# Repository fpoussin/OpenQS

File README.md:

OpenQS
======

OSHW quick-shifter.

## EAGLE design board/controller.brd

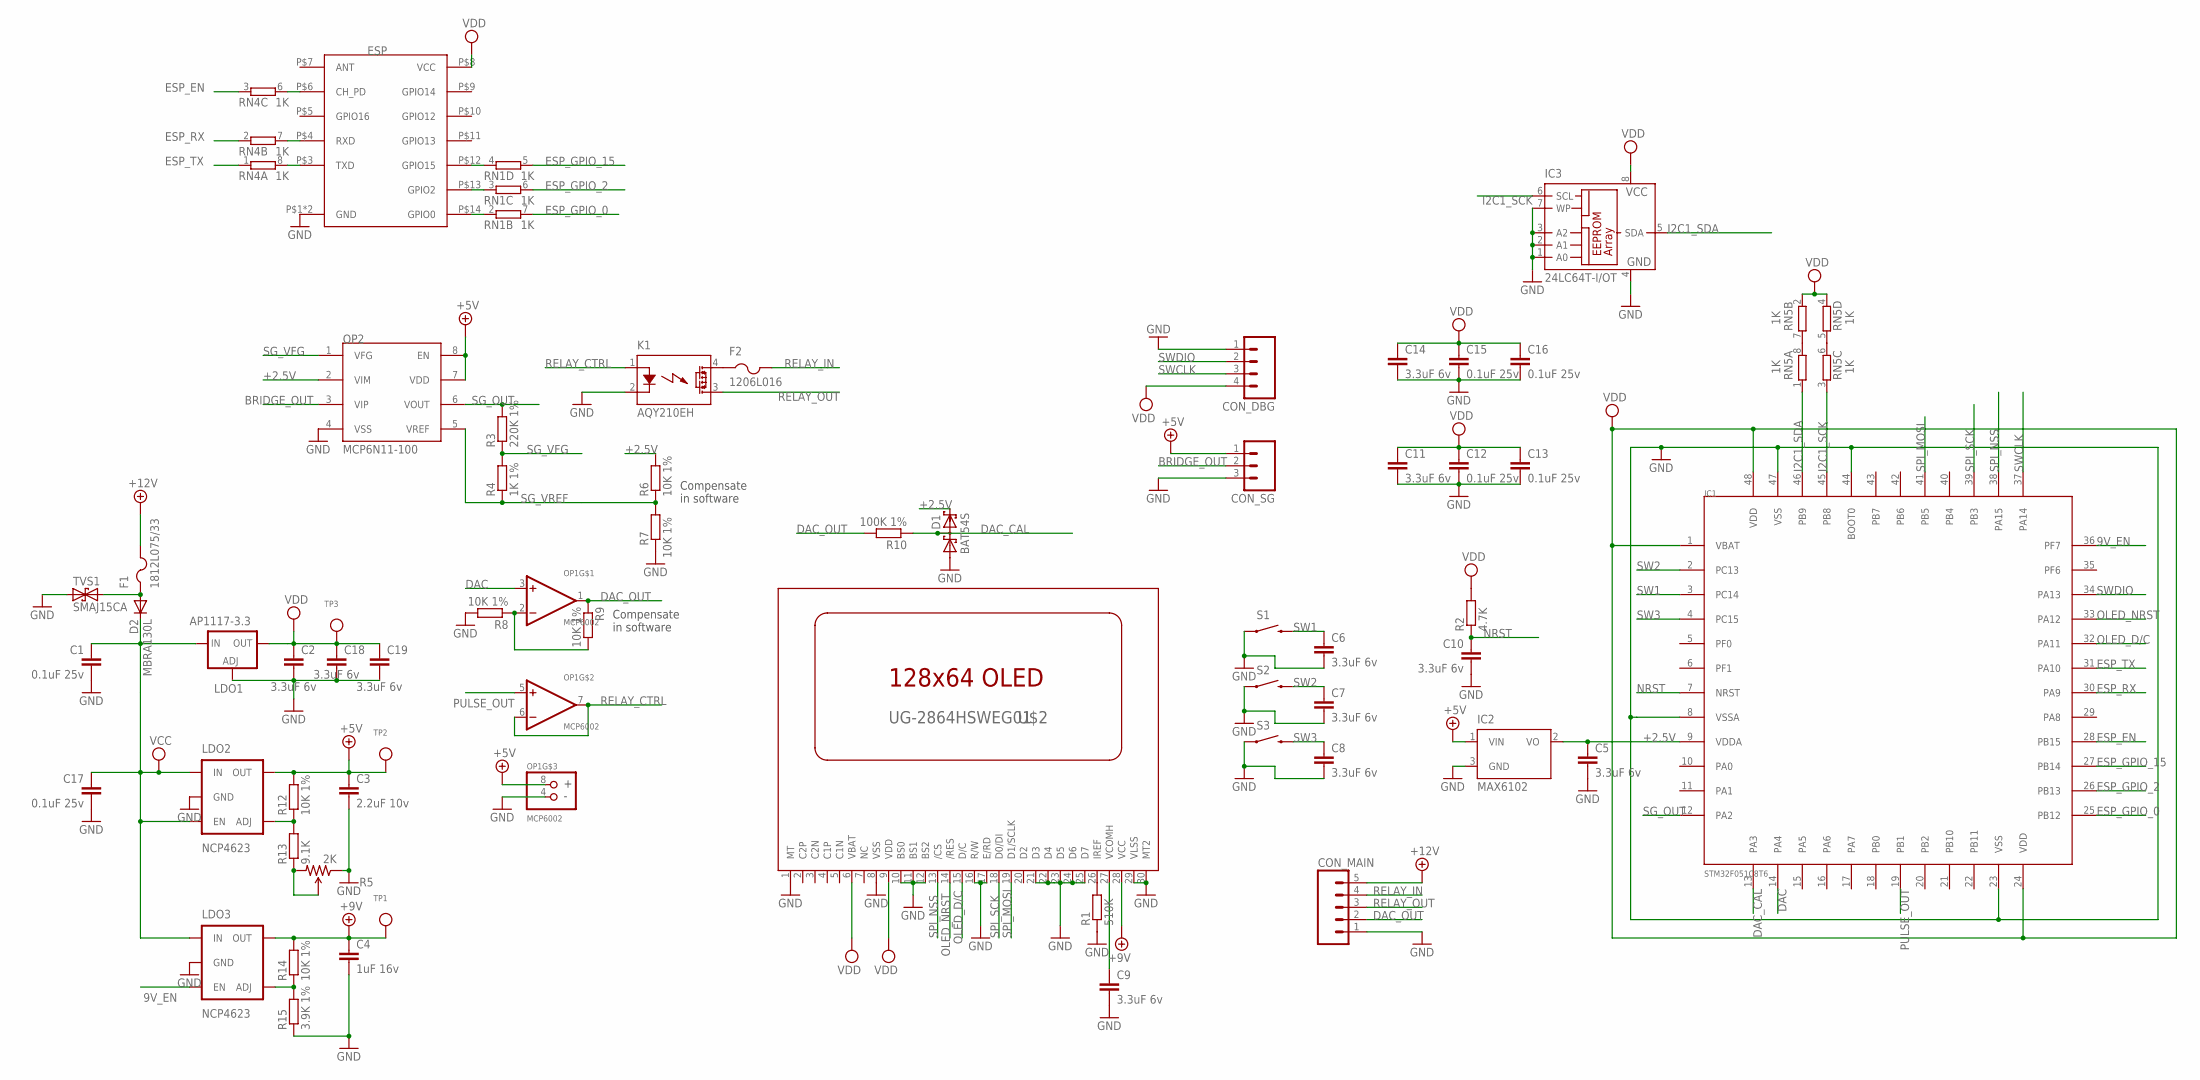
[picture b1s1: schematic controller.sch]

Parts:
C1, C12, C13, C15, C16, C17: 0.1uF 25v; C0603
C2, C5, C6, C7, C8, C9, C10, C11, C14, C18, C19: 3.3uF 6v; C0603
C3: 2.2uF 10v; C0603
C4: 1uF 16v; C0603
CON_DBG: M04LOCK; 1X04_LOCK
CON_MAIN: M05LOCK; 1X05_LOCK
CON_SG: M03LOCK; 1X03_LOCK
D1: BAT54S; SOT23
D2: MBRA130L; SMA-DIODE
ESP: ESP8266; ESP-03
F1: 1812L075/33; 1812
F2: 1206L016; R1206
IC1: STM32F051C8T6; LQFP-48
IC2: MAX6102; SOT23
IC3: 24LC64T-I/OT; SO-08
K1: AQY210EH; SOP04
LDO1: AP1117-3.3; DPACK
LDO2, LDO3: NCP4623; SOT23-5
OP1: MCP6002; MSOP-8
OP2: MCP6N11-100; SO08
R1: 510K; R0603
R2: 4.7K; R0603
R3: 220K 1%; R0603
R4: 1K 1%; R0603
R5: 2K; TRIMPOT-3MM-2
R6, R7, R8, R9, R12, R14: 10K 1%; R0603
R10: 100K 1%; R0603
R13: 9.1K; R0603
R15: 3.9K 1%; R0603
RN1, RN4, RN5: 1K; CAY16
S1, S2, S3: SWITCH-MOMENTARY-2SMD-2; TACTILE_SWITCH_SMD-2
TP1, TP2, TP3: TESTPOINTROUND2MM; TESTPOINT_ROUND_2MM
TVS1: SMAJ15CA; SMA-DIODE
U$2: UG-2864HSWEG01; 1X30-0.7MM

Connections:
9V_EN: IC1.36 (PF7), LDO3.5 (EN)
+2.5V: C5.1, D1.2 (C2), IC1.9 (VDDA), IC2.2 (VO), OP2.2 (VIM), R6.2
+5V: C3.1, CON_SG.1, IC2.1 (VIN), LDO2.1 (OUT), OP1.8 (+), OP2.7 (VDD), OP2.8 (EN), R12.2, TP2.P$1
+9V: C4.1, LDO3.1 (OUT), R14.2, TP1.P$1, U$2.28 (VCC)
+12V: CON_MAIN.5, F1.2
BRIDGE_OUT: CON_SG.2, OP2.3 (VIP)
DAC: IC1.14 (PA4), OP1.3 (+IN)
DAC_CAL: D1.3 (C1A2), IC1.13 (PA3), R10.1
DAC_OUT: CON_MAIN.2, OP1.1 (OUT), R9.1, R10.2
ESP_EN: IC1.28 (PB15), RN4.3 (1)
ESP_GPIO_0: IC1.25 (PB12), RN1.7 (2)
ESP_GPIO_2: IC1.26 (PB13), RN1.6 (2)
ESP_GPIO_15: IC1.27 (PB14), RN1.5 (2)
ESP_RX: IC1.30 (PA9), RN4.2 (1)
ESP_TX: IC1.31 (PA10), RN4.1
GND: C1.2, C2.2, C3.2, C4.2, C5.2, C6.2, C7.2, C8.2, C9.2, C10.2, C11.2, C12.2, C13.2, C14.2, C15.2, C16.2, C17.2, C18.2, C19.2, CON_DBG.1, CON_MAIN.1, CON_SG.3, D1.1 (A1), ESP.P$1 (GND), ESP.P$2 (GND), IC1.8 (VSSA), IC1.23 (VSS), IC1.44 (BOOT0), IC1.47 (VSS), IC2.3 (GND), IC3.1 (A0), IC3.2 (A1), IC3.3 (A2), IC3.4 (GND), IC3.7 (WP), K1.2 (K), LDO1.1 (ADJ), LDO2.2 (GND), LDO3.2 (GND), OP1.4 (-), OP2.4 (VSS), R1.1, R5.1 (CCW), R7.1, R8.2, R15.1, S1.2 (1), S2.2 (1), S3.2 (1), TVS1.A (1), U$2.1 (MT), U$2.8 (VSS), U$2.10 (BS0), U$2.11 (BS1), U$2.12 (BS2), U$2.16 (R/W), U$2.17 (E/RD), U$2.21 (D3), U$2.22 (D4), U$2.23 (D5), U$2.24 (D6), U$2.25 (D7), U$2.29 (VLSS), U$2.30 (MT2)
I2C1_SCK: IC1.45 (PB8), IC3.6 (SCL), RN5.3 (1)
I2C1_SDA: IC1.46 (PB9), IC3.5 (SDA), RN5.1
unnamed: OP1.2 (-IN), R8.1, R9.2
unnamed: C9.1, U$2.27 (VCOMH)
unnamed: R1.2, U$2.26 (IREF)
unnamed: D2.A, F1.1, TVS1.C (2)
unnamed: F2.1, K1.4 (DS1)
unnamed: LDO2.4 (ADJ), R12.1, R13.2
unnamed: LDO3.4 (ADJ), R14.1, R15.2
unnamed: R5.2 (WIPER), R5.3 (CW), R13.1
unnamed: ESP.P$14 (GPIO0), RN1.2 (1)
unnamed: ESP.P$13 (GPIO2), RN1.3 (1)
unnamed: ESP.P$12 (GPIO15), RN1.4 (1)
unnamed: ESP.P$3 (TXD), RN4.8 (2)
unnamed: ESP.P$6 (CH_PD), RN4.6 (2)
unnamed: ESP.P$4 (RXD), RN4.7 (2)
unnamed: RN5.7 (2), RN5.8 (2)
unnamed: RN5.5 (2), RN5.6 (2)
NRST: C10.1, IC1.7 (NRST), R2.1
OLED_D/C: IC1.32 (PA11), U$2.15 (D/C)
OLED_NRST: IC1.33 (PA12), U$2.14 (/RES)
PULSE_OUT: IC1.19 (PB1), OP1.5 (+IN)
RELAY_CTRL: K1.1 (A), OP1.6 (-IN), OP1.7 (OUT)
RELAY_IN: CON_MAIN.4, F2.2
RELAY_OUT: CON_MAIN.3, K1.3 (DS2)
SG_OUT: IC1.12 (PA2), OP2.6 (VOUT), R3.2
SG_VFG: OP2.1 (VFG), R3.1, R4.2
SG_VREF: OP2.5 (VREF), R4.1, R6.1, R7.2
SPI_MOSI: IC1.41 (PB5), U$2.19 (D1/SCLK)
SPI_NSS: IC1.38 (PA15), U$2.13 (/CS)
SPI_SCK: IC1.39 (PB3), U$2.18 (D0/DI)
SW1: C6.1, IC1.3 (PC14), S1.1 (2)
SW2: C7.1, IC1.2 (PC13), S2.1 (2)
SW3: C8.1, IC1.4 (PC15), S3.1 (2)
SWCLK: CON_DBG.3, IC1.37 (PA14)
SWDIO: CON_DBG.2, IC1.34 (PA13)
VCC: C1.1, C17.1, D2.C, LDO1.3 (IN), LDO2.3 (IN), LDO2.5 (EN), LDO3.3 (IN)
VDD: C2.1, C11.1, C12.1, C13.1, C14.1, C15.1, C16.1, C18.1, C19.1, CON_DBG.4, ESP.P$8 (VCC), IC1.1 (VBAT), IC1.24 (VDD), IC1.48 (VDD), IC3.8 (VCC), LDO1.4 (OUT), R2.2, RN5.2 (1), RN5.4 (1), TP3.P$1, U$2.6 (VBAT), U$2.9 (VDD)

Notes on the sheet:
Compensate in software

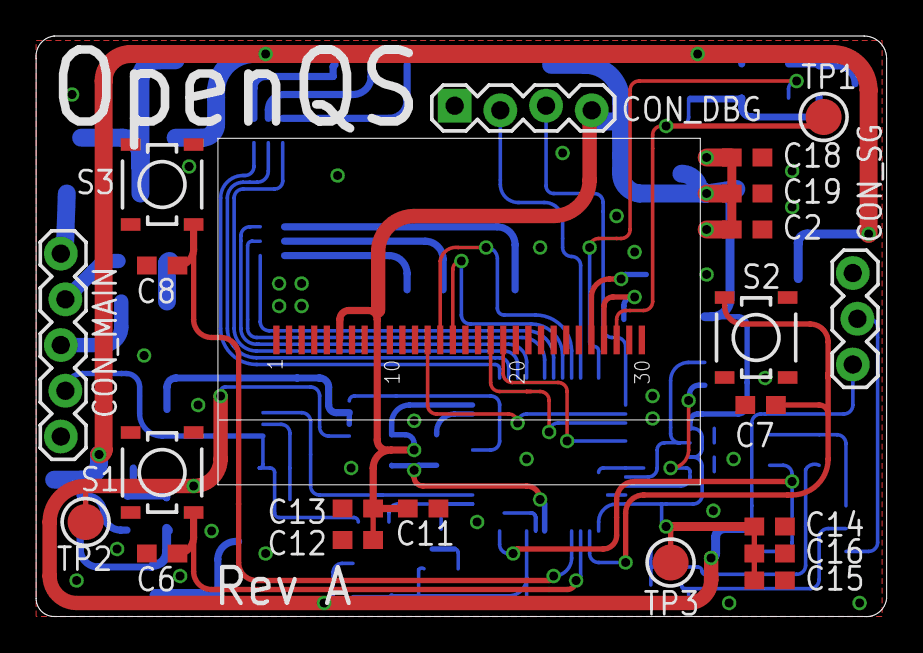
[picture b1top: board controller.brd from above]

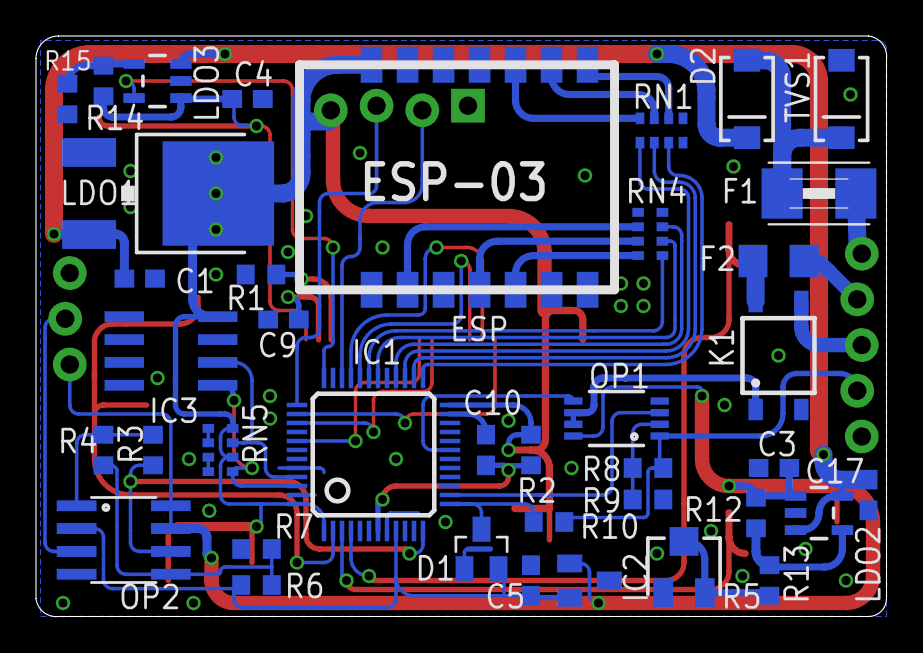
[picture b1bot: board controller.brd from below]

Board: 2 copper layers, 47.3 x 32.3 mm, 61 parts (39 on the bottom side), 54 nets.

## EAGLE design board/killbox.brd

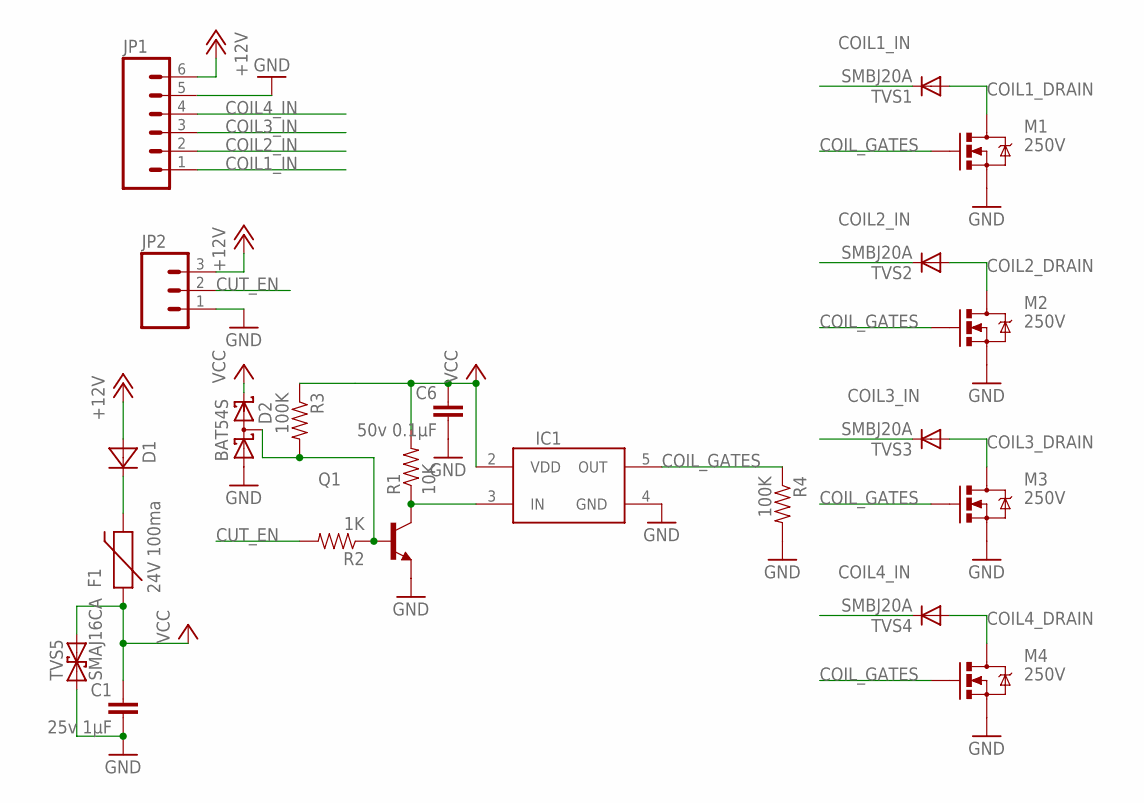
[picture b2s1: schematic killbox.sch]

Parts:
C1: 25v 1µF; 0603-CAP
C6: 50v 0.1µF; 0603-CAP
D1: MBRA340T3; SMA
D2: BAT54S; SOT23
F1: 24V 100ma; PTC-1206
IC1: MCP1416; SOT23-5
JP1: M063.5MM-6; SCREWTERMINAL-3.5MM-6
JP2: M03-SCREW-5MM; SCREWTERMINAL-5MM-3
M1, M2, M3, M4: 250V; DPAK
Q1: MMBT2222ALT1-NPN-SOT23-BEC; SOT23-BEC
R1: 10K; 0603-RES
R2: 1K; 0603-RES
R3, R4: 100K; 0603-RES
TVS1, TVS2, TVS3, TVS4: SMBJ20A; SMB-DIODE
TVS5: SMAJ16CA; SMA-DIODE

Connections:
+12V: D1.A, JP1.6, JP2.3
COIL1_DRAIN: M1.4 (D), TVS1.A
COIL1_IN: JP1.1, TVS1.C
COIL2_DRAIN: M2.4 (D), TVS2.A
COIL2_IN: JP1.2, TVS2.C
COIL3_DRAIN: M3.4 (D), TVS3.A
COIL3_IN: JP1.3, TVS3.C
COIL4_DRAIN: M4.4 (D), TVS4.A
COIL4_IN: JP1.4, TVS4.C
COIL_GATES: IC1.5 (OUT), M1.1 (G), M2.1 (G), M3.1 (G), M4.1 (G), R4.1
CUT_EN: JP2.2, R2.2
GND: C1.2, C6.2, D2.1 (A1), IC1.4 (GND), JP1.5, JP2.1, M1.3 (S), M2.3 (S), M3.3 (S), M4.3 (S), Q1.E, R4.2, TVS5.A (1)
unnamed: IC1.3 (IN), Q1.C, R1.1
unnamed: D2.3 (C1A2), Q1.B, R2.1, R3.2
unnamed: D1.C, F1.2
VCC: C1.1, C6.1, D2.2 (C2), F1.1, IC1.2 (VDD), R1.2, R3.1, TVS5.C (2)

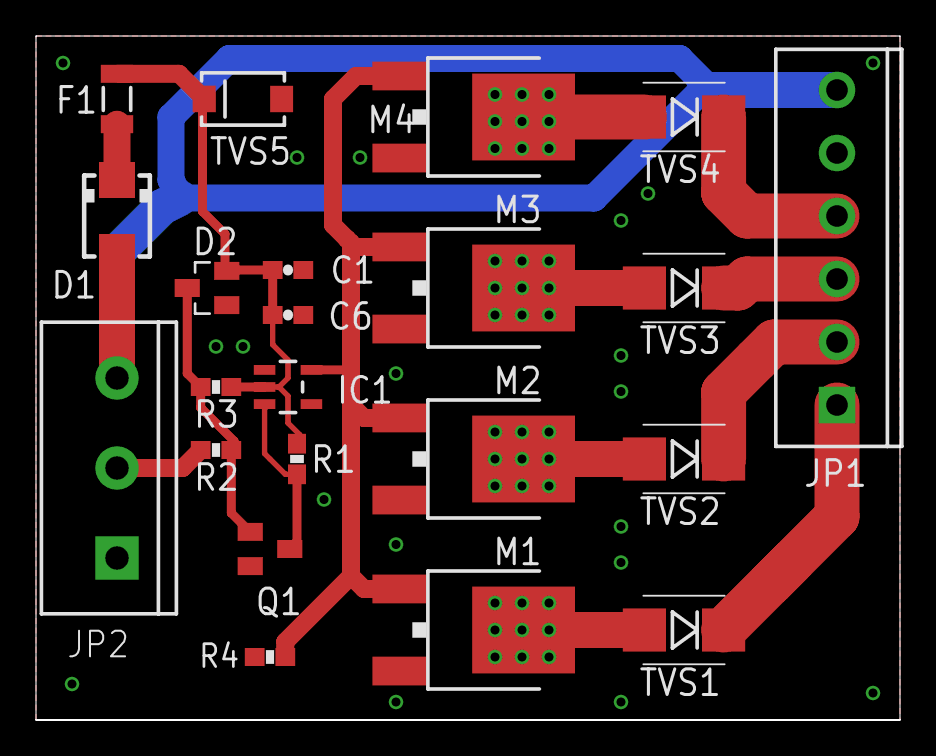
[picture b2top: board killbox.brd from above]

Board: 2 copper layers, 48.0 x 38.0 mm, 22 parts (0 on the bottom side), 16 nets.

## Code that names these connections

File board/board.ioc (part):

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Mcu.Name=STM32F051C6Tx
Mcu.Package=LQFP48
Mcu.UserName=STM32F051C6Tx
PA10.Mode=Asynchronous
PA10.Signal=USART1_RX
PA11.GPIOParameters=GPIO_Label
PA11.GPIO_Label=OLED_D/C
PA11.Signal=GPIO_Output
PA12.GPIOParameters=GPIO_Label
PA12.GPIO_Label=OLED_NRST
PA12.Signal=GPIO_Output
PA13.Mode=Serial-WireDebug
PA13.Signal=SYS_SWDIO
PA14.Mode=Serial-WireDebug
PA14.Signal=SYS_SWCLK
PA15.Mode=NSS_Signal_Hard
PA15.Signal=SPI1_NSS
PA2.Mode=IN2
PA2.Signal=ADC_IN2
PA4.Signal=COMP_DAC11_group
PA9.Mode=Asynchronous
PA9.Signal=USART1_TX
PB1.GPIOParameters=GPIO_Label
PB1.GPIO_Label=PULSE_OUT
PB1.Signal=S_TIM3_CH4
PB12.GPIOParameters=GPIO_Label
PB12.GPIO_Label=ESP_GPIO0
PB12.Signal=GPIO_Output
PB13.GPIOParameters=GPIO_Label
PB13.GPIO_Label=ESP_GPIO2
PB13.Signal=GPIO_Output
PB14.GPIOParameters=GPIO_Label
PB14.GPIO_Label=ESP_GPIO15
PB14.Signal=GPIO_Output
PB15.GPIOParameters=GPIO_Label
PB15.GPIO_Label=ESP_EN
PB15.Signal=GPIO_Output
PB3.Mode=TX_Only_Simplex_Unidirect_Master
PB3.Signal=SPI1_SCK
PB5.Mode=TX_Only_Simplex_Unidirect_Master
PB5.Signal=SPI1_MOSI
PB8.Mode=I2C
PB8.Signal=I2C1_SCL
PB9.Mode=I2C
PB9.Signal=I2C1_SDA
PC13.GPIOParameters=GPIO_Label
PC13.GPIO_Label=SW2
PC13.Signal=GPIO_Input
PC14-OSC32_IN.GPIOParameters=GPIO_Label
PC14-OSC32_IN.GPIO_Label=SW1
PC14-OSC32_IN.Signal=GPIO_Input
PC15-OSC32_OUT.GPIOParameters=GPIO_Label
PC15-OSC32_OUT.GPIO_Label=SW3
PC15-OSC32_OUT.Signal=GPIO_Input
PF7.GPIOParameters=GPIO_Label
PF7.GPIO_Label=9V_EN
PF7.Signal=GPIO_Output
RCC.HSE_VALUE=16000000
RCC.SYSCLKSource=RCC_SYSCLKSOURCE_PLLCLK

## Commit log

2014-10-26 Updating makefiles for ESP

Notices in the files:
parts and their libraries:
SparkFun-DiscreteSemi: Licensing: Creative Commons ShareAlike 4.0 International - https://creativecommons.org/licenses/by-sa/4.0
SparkFun: Licensing: CC v3.0 Share-Alike You are welcome to use this library for commercial purposes.
